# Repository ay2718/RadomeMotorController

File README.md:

# Radome motor controller

## CAN protocol

The Radome CAN protocol is very simple.  Send azimuth commands to address 0x1 and elevation commands to address 0x2.  Azimuth and elevation reply back from addresses 0x101 and 0x102 respectively.  Any packet sent to address 0x0 will trigger both azimuth and elevation to reply back with their current status without initiating a motor movement, sending commands will also trigger a reply back.

Even if you feed the CAN total garbage the dish will not exceed safe positions (for elevation), speeds, or acceleration.

The controllers must be updated at least every 100 ms or faster. Othewise they will safely bring the dish to a halt.

The command structure is as follows:

```
Transmit:
// 2^24 is 360 degrees, position is unsigned
tx byte 0 = position bits 23:16
tx byte 1 = position bits 15:8
tx byte 2 = position bits 7:0

// LSB is 1 arcsecond/s = 1/1200 dps, signed
tx byte 3 = velocity bits 15:8
tx byte 4 = velocity bits 7:0

Receive:
// 2^24 is 360 degrees, position is unsigned
rx byte 0 = position bits 23:16
rx byte 1 = position bits 15:8
rx byte 2 = position bits 7:0

// LSB is 1 arcsecond/s = 1/1200 dps, signed
rx byte 3 = velocity bits 15:8
rx byte 4 = velocity bits 7:0

// LSB is 1 mA, signed
rx byte 5 = current bits 15:8
rx byte 6 = current bits 7:0

// LSB is 0.5V, unsigned
rx byte 7 = bus voltage bits 7:0
```

I recommend casting position as a `uint32_t` such that 2<sup>32</sup> is equivalent to 360 degrees.  This makes position math very nice since overflow lines up with one rotation.

We feed the dish position *and* velocity because the velocity information in order to generate very smooth trajectories.  If you want to command a position and you don't care much about timing, it's fine to send a position command with zero velocity.  If you're tracking a satellite moving a couple degrees per second across the sky on X band, the velocity really helps (empirically we were able to maintain 0.05 degrees of tracking error up to 10 dps or so)

## Firmware overview

If you decide to build the firmware, this is an STM32CubeIDE project.  You may need to enable floating point support for printf.  Define or underine azimuth or elevation in Core/Inc/main.h to set azimuth or elevation.  Encoder offsets are hardcoded in.

## CAN Bootloader usage

`az_bootloader.bin` and `el_bootloader.bin` should already be loaded onto their respective motor drives.  The bootloader takes up 2 flash pages on each drive (4 kB)

`flash_motor.py` is used to upload firmware over CAN bus.  The baud rate is 125000 (same as for operating the drives).

Example usage: `./flash_motor.py` --id 0x01  -f radome_azimuth.bin`.
The `--id` flag selects which drive to write toe (0x01 is azimuth, 0x02 is elevation) and the `-f` or `--filename` flag selects the binfile to upload.

If a motor drive is unresponsive to being flashed, try running `./flash_motor.py ...`, leave it running, and cycle power to the motor drives.  This is useful if there's a problem with the firmware--`flash_motor.py` sends out pings to each motor's address every 100ms and the drives wait for pings in bootloader mode for 500ms before starting up.

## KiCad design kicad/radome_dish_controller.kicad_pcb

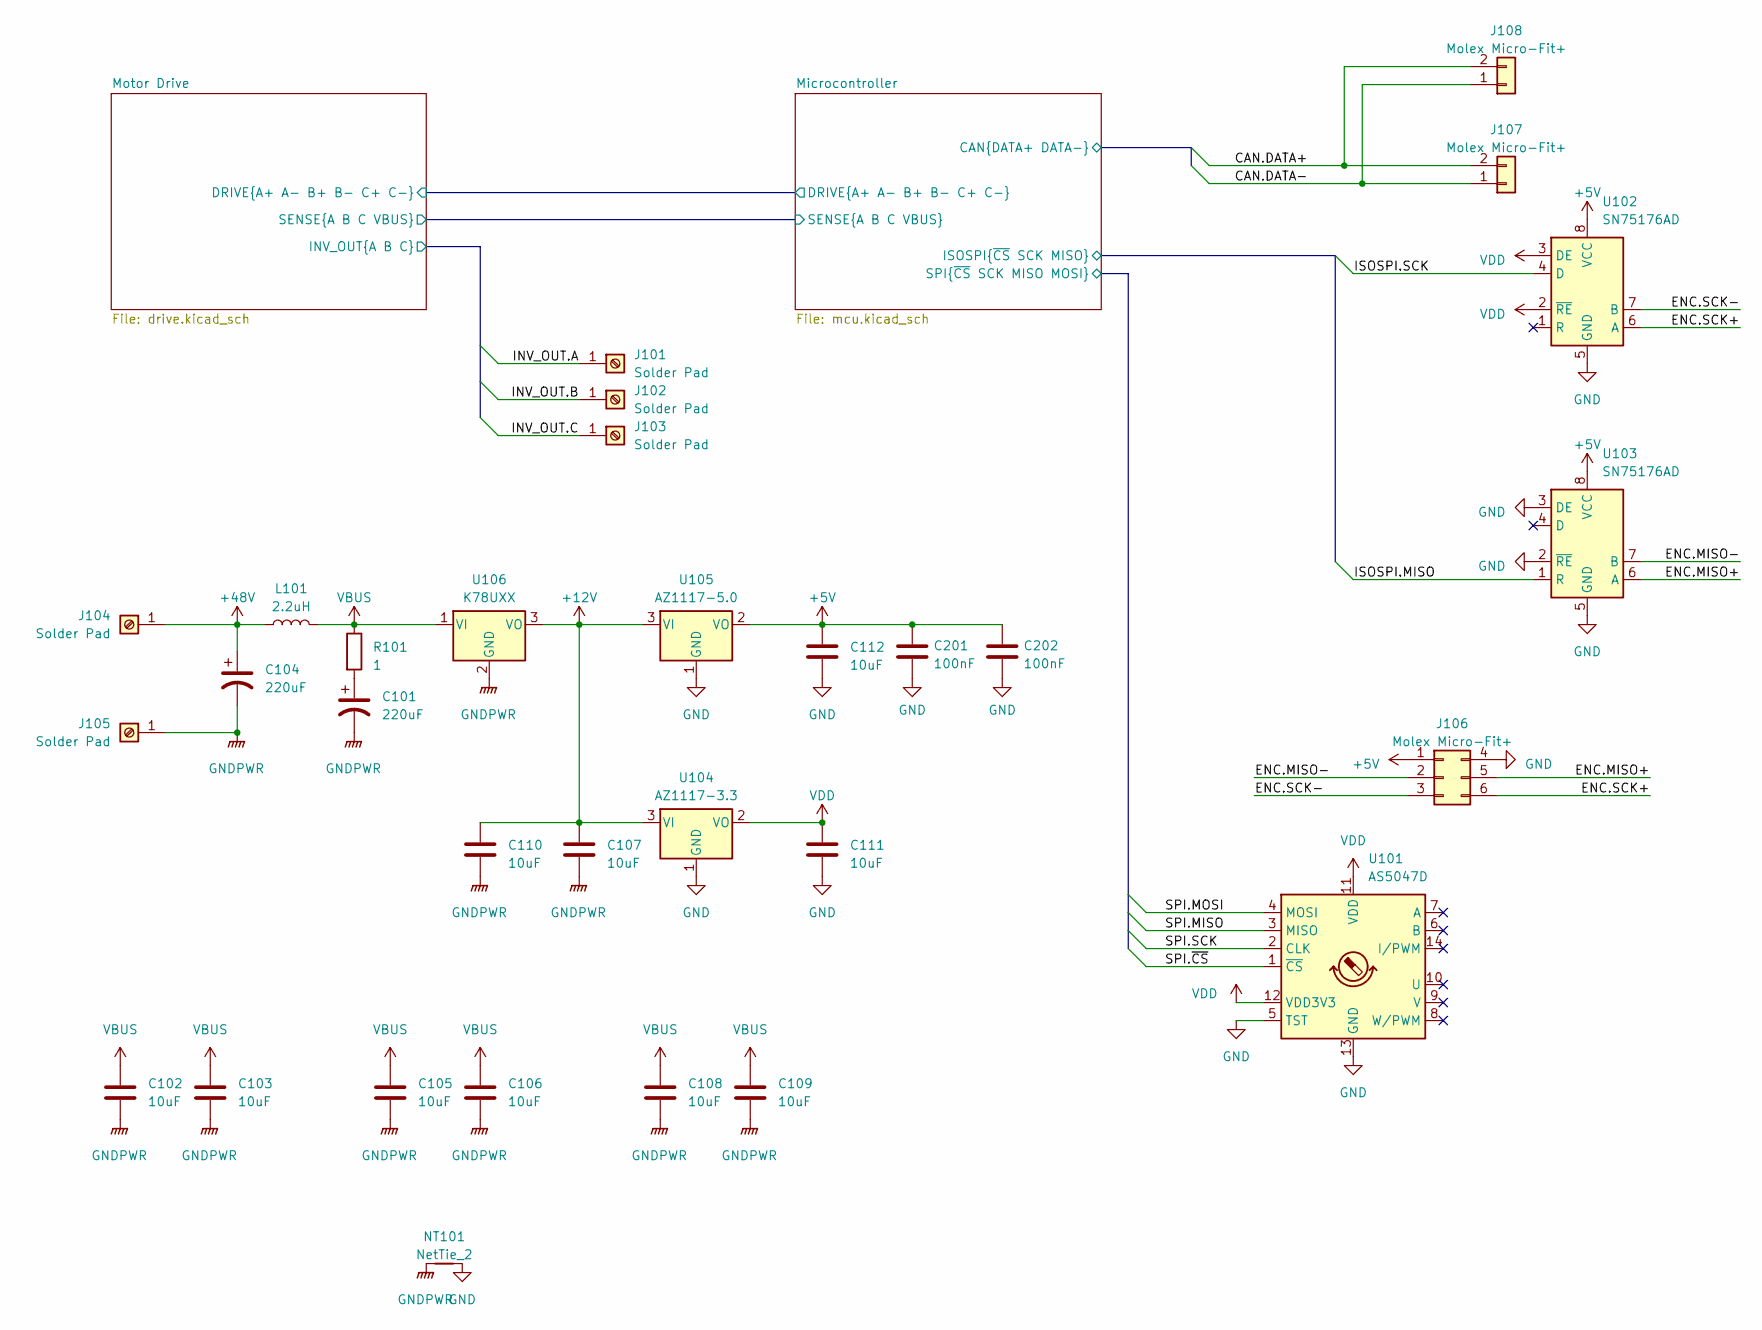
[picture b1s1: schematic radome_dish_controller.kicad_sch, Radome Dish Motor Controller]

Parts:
C101, C104: 220uF; CP_Radial_D12.5mm_P5.00mm
C102, C103, C105, C106, C108, C109: 10uF; C_2220_5650Metric; LCSC C153035
C107, C110, C111, C112: 10uF; C_1206_3216Metric; LCSC C13585
C201, C202: 100nF; C_0603_1608Metric; digikeypn 1276-1935-1-ND
J101, J102, J103, J104, J105: Solder Pad; SolderWirePad_1x01_SMD_5x10mm
J106: Molex Micro-Fit+; MOLEX_2068320602
J107, J108: Molex Micro-Fit+; MOLEX_2165711002
L101: 2.2uH; L_Vishay_IHLP-5050; LCSC C845090
NT101: NetTie_2; NetTie-2_SMD_Pad2.0mm
R101: 1; R_2512_6332Metric; LCSC C11254
U101: AS5047D; TSSOP-14_4.4x5mm_P0.65mm; LCSC C962063
U102, U103: SN75176AD; SOIC-8_3.9x4.9mm_P1.27mm; LCSC C468242
U104: AZ1117-3.3; SOT-223-3_TabPin2; LCSC C435835
U105: AZ1117-5.0; SOT-223-3_TabPin2; LCSC C526405
U106: K78UXX; K78UXX-RightAngle

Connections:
+12V: C107.1, C110.1, U104.3 (VI), U105.3 (VI), U106.3 (VO); also elsewhere on the board
+48V: C104.1, J104.1, L101.1
/ENC.MISO+: J106.5, U103.6 (A)
/ENC.MISO-: J106.2, U103.7 (B)
/ENC.SCK+: J106.6, U102.6 (A)
/ENC.SCK-: J106.3, U102.7 (B)
/Microcontroller/CAN.DATA+: J107.2, J108.2; also elsewhere on the board
/Microcontroller/CAN.DATA-: J107.1, J108.1; also elsewhere on the board
/Microcontroller/ISOSPI.MISO: U103.1 (R); also elsewhere on the board
/Microcontroller/ISOSPI.SCK: U102.4 (D); also elsewhere on the board
/Microcontroller/SPI.MISO: U101.3 (MISO); also elsewhere on the board
/Microcontroller/SPI.MOSI: U101.4 (MOSI); also elsewhere on the board
/Microcontroller/SPI.SCK: U101.2 (CLK); also elsewhere on the board
/Microcontroller/SPI.~CS: U101.1 (~CS); also elsewhere on the board
/Motor Drive/INV_OUT.A: J101.1; also elsewhere on the board
/Motor Drive/INV_OUT.B: J102.1; also elsewhere on the board
/Motor Drive/INV_OUT.C: J103.1; also elsewhere on the board
GND: C111.2, C112.2, C201.2, C202.2, J106.4, NT101.2, U101.5 (TST), U101.13 (GND), U102.5 (GND), U103.2 (~RE), U103.3 (DE), U103.5 (GND), U104.1 (GND), U105.1 (GND); also elsewhere on the board
GNDPWR: C101.2, C102.2, C103.2, C104.2, C105.2, C106.2, C107.2, C108.2, C109.2, C110.2, J105.1, NT101.1, U106.2 (GND); also elsewhere on the board
unnamed: C101.1, R101.2
VBUS: C102.1, C103.1, C105.1, C106.1, C108.1, C109.1, L101.2, R101.1, U106.1 (VI); also elsewhere on the board

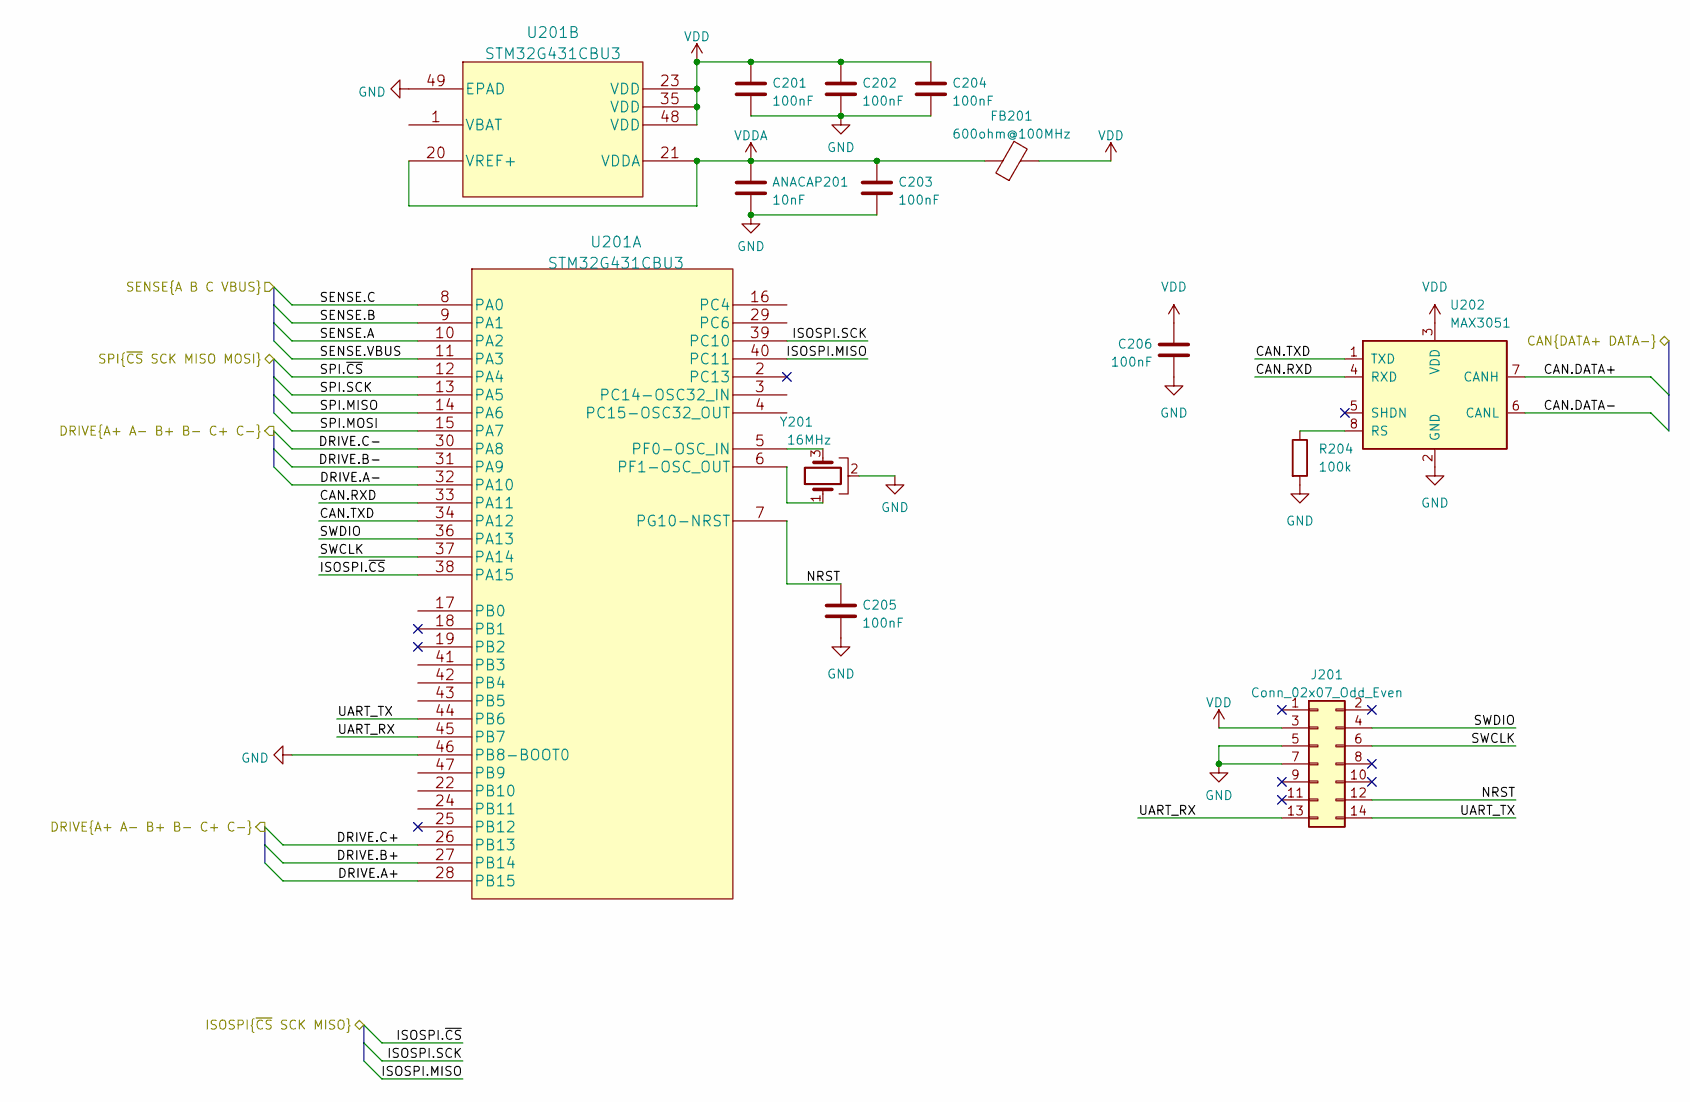
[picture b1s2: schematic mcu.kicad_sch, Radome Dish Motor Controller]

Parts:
ANACAP201: 10nF; C_0603_1608Metric; digikeypn 1276-1009-1-ND
C201, C202, C203, C204, C205, C206: 100nF; C_0603_1608Metric; digikeypn 1276-1935-1-ND
FB201: 600ohm@100MHz; L_0603_1608Metric; digikeypn 732-1593-1-ND
J201: Conn_02x07_Odd_Even; PinHeader_2x07_P1.27mm_Vertical_SMD; digikeypn 1175-1736-ND
R204: 100k; R_0603_1608Metric; LCSC C25803
U201: STM32G431CBU3; QFN-48-1EP_7x7mm_P0.5mm_EP5.3x5.3mm; digikeypn STM32G431CBU3-ND
U202: MAX3051; SO-8_3.9x4.9mm_P1.27mm; LCSC C15648
Y201: 16MHz; Resonator_SMD_Murata_CSTxExxV-3Pin_3.0x1.1mm; digikeypn 490-17948-1-ND

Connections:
/Microcontroller/CAN.DATA+: U202.7 (CANH); also elsewhere on the board
/Microcontroller/CAN.DATA-: U202.6 (CANL); also elsewhere on the board
/Microcontroller/CAN.RXD: U201.33 (PA11), U202.4 (RXD)
/Microcontroller/CAN.TXD: U201.34 (PA12), U202.1 (TXD)
/Microcontroller/DRIVE.A+: U201.28 (PB15); also elsewhere on the board
/Microcontroller/DRIVE.A-: U201.32 (PA10); also elsewhere on the board
/Microcontroller/DRIVE.B+: U201.27 (PB14); also elsewhere on the board
/Microcontroller/DRIVE.B-: U201.31 (PA9); also elsewhere on the board
/Microcontroller/DRIVE.C+: U201.26 (PB13); also elsewhere on the board
/Microcontroller/DRIVE.C-: U201.30 (PA8); also elsewhere on the board
/Microcontroller/ISOSPI.MISO: U201.40 (PC11); also elsewhere on the board
/Microcontroller/ISOSPI.SCK: U201.39 (PC10); also elsewhere on the board
/Microcontroller/ISOSPI.~CS: U201.38 (PA15)
/Microcontroller/NRST: C205.1, J201.12, U201.7 (PG10-NRST)
/Microcontroller/SENSE.A: U201.10 (PA2); also elsewhere on the board
/Microcontroller/SENSE.B: U201.9 (PA1); also elsewhere on the board
/Microcontroller/SENSE.C: U201.8 (PA0); also elsewhere on the board
/Microcontroller/SENSE.VBUS: U201.11 (PA3); also elsewhere on the board
/Microcontroller/SPI.MISO: U201.14 (PA6); also elsewhere on the board
/Microcontroller/SPI.MOSI: U201.15 (PA7); also elsewhere on the board
/Microcontroller/SPI.SCK: U201.13 (PA5); also elsewhere on the board
/Microcontroller/SPI.~CS: U201.12 (PA4); also elsewhere on the board
/Microcontroller/SWCLK: J201.6, U201.37 (PA14)
/Microcontroller/SWDIO: J201.4, U201.36 (PA13)
/Microcontroller/UART_RX: J201.13, U201.45 (PB7)
/Microcontroller/UART_TX: J201.14, U201.44 (PB6)
GND: ANACAP201.2, C201.2, C202.2, C203.2, C204.2, C205.2, C206.2, J201.5, J201.7, R204.2, U201.46 (PB8-BOOT0), U201.49 (EPAD), U202.2 (GND), Y201.2; also elsewhere on the board
unnamed: U201.5 (PF0-OSC_IN), Y201.3
unnamed: U201.6 (PF1-OSC_OUT), Y201.1
unnamed: R204.1, U202.8 (RS)
VDDA: ANACAP201.1, C203.1, FB201.1, U201.20 (VREF+), U201.21 (VDDA)

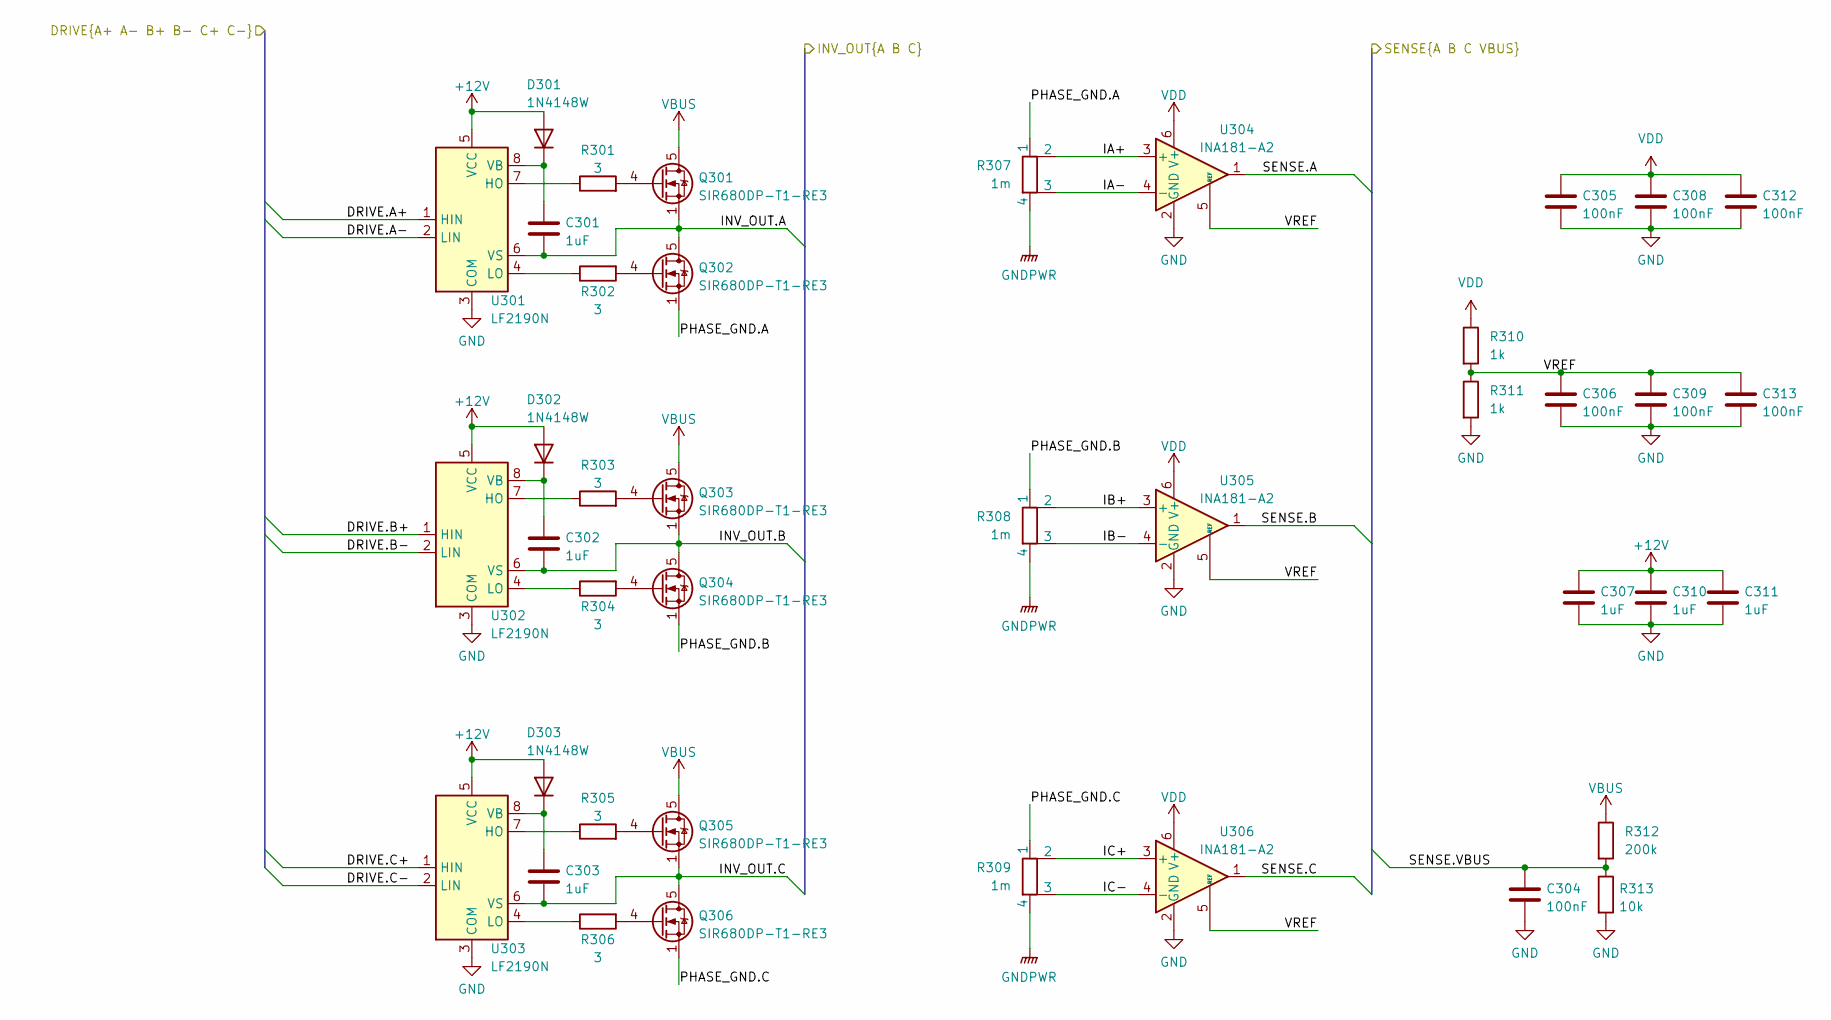
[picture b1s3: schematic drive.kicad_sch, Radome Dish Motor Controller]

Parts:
C301, C302, C303, C307, C310, C311: 1uF; C_0603_1608Metric; digikeypn 1276-1860-1-ND
C304, C305, C306, C308, C309, C312, C313: 100nF; C_0603_1608Metric; digikeypn 1276-1935-1-ND
D301, D302, D303: 1N4148W; D_SOD-123; digikeypn 1N4148W-13FDICT-ND
Q301, Q302, Q303, Q304, Q305, Q306: SIR680DP-T1-RE3; PowerPAK_SO-8_Single; digikeypn SIR426DP-T1-GE3CT-ND
R301, R302, R303, R304, R305, R306: 3; R_0603_1608Metric; digikeypn RMCF0603FT3R00CT-ND
R307, R308, R309: 1m; R_Shunt_Vishay_WSK2512_6332Metric_T2.21mm; LCSC C459678
R310, R311: 1k; R_0603_1608Metric; digikeypn RMCF0603FT10K0CT-ND
R312: 200k; R_0603_1608Metric; digikeypn CR0603-FX-5102ELFCT-ND
R313: 10k; R_0603_1608Metric; digikeypn RMCF0603FT10K0CT-ND
U301, U302, U303: LF2190N; SOIC-8_3.9x4.9mm_P1.27mm; digikeypn 212-LF2190NTRCT-ND
U304, U305, U306: INA181-A2; SOT-23-6; digikeypn 296-47657-1-ND

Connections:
+12V: C307.1, C310.1, C311.1, D301.2 (A), D302.2 (A), D303.2 (A), U301.5 (VCC), U302.5 (VCC), U303.5 (VCC); also elsewhere on the board
/Microcontroller/DRIVE.A+: U301.1 (HIN); also elsewhere on the board
/Microcontroller/DRIVE.A-: U301.2 (LIN); also elsewhere on the board
/Microcontroller/DRIVE.B+: U302.1 (HIN); also elsewhere on the board
/Microcontroller/DRIVE.B-: U302.2 (LIN); also elsewhere on the board
/Microcontroller/DRIVE.C+: U303.1 (HIN); also elsewhere on the board
/Microcontroller/DRIVE.C-: U303.2 (LIN); also elsewhere on the board
/Microcontroller/SENSE.A: U304.1; also elsewhere on the board
/Microcontroller/SENSE.B: U305.1; also elsewhere on the board
/Microcontroller/SENSE.C: U306.1; also elsewhere on the board
/Microcontroller/SENSE.VBUS: C304.1, R312.2, R313.1; also elsewhere on the board
/Motor Drive/IA+: R307.2, U304.3 (+)
/Motor Drive/IA-: R307.3, U304.4 (-)
/Motor Drive/IB+: R308.2, U305.3 (+)
/Motor Drive/IB-: R308.3, U305.4 (-)
/Motor Drive/IC+: R309.2, U306.3 (+)
/Motor Drive/IC-: R309.3, U306.4 (-)
/Motor Drive/INV_OUT.A: C301.2, Q301.1 (S), Q301.2 (S), Q301.3 (S), Q302.5 (D), U301.6 (VS); also elsewhere on the board
/Motor Drive/INV_OUT.B: C302.2, Q303.1 (S), Q303.2 (S), Q303.3 (S), Q304.5 (D), U302.6 (VS); also elsewhere on the board
/Motor Drive/INV_OUT.C: C303.2, Q305.1 (S), Q305.2 (S), Q305.3 (S), Q306.5 (D), U303.6 (VS); also elsewhere on the board
/Motor Drive/PHASE_GND.A: Q302.1 (S), Q302.2 (S), Q302.3 (S), R307.1
/Motor Drive/PHASE_GND.B: Q304.1 (S), Q304.2 (S), Q304.3 (S), R308.1
/Motor Drive/PHASE_GND.C: Q306.1 (S), Q306.2 (S), Q306.3 (S), R309.1
/Motor Drive/VREF: C306.1, C309.1, C313.1, R310.2, R311.1, U304.5 (REF), U305.5 (REF), U306.5 (REF)
GND: C304.2, C305.2, C306.2, C307.2, C308.2, C309.2, C310.2, C311.2, C312.2, C313.2, R311.2, R313.2, U301.3 (COM), U302.3 (COM), U303.3 (COM), U304.2 (GND), U305.2 (GND), U306.2 (GND); also elsewhere on the board
GNDPWR: R307.4, R308.4, R309.4; also elsewhere on the board
unnamed: C301.1, D301.1 (K), U301.8 (VB)
unnamed: C302.1, D302.1 (K), U302.8 (VB)
unnamed: C303.1, D303.1 (K), U303.8 (VB)
unnamed: Q301.4 (G), R301.2
unnamed: Q302.4 (G), R302.2
unnamed: Q303.4 (G), R303.2
unnamed: Q304.4 (G), R304.2
unnamed: Q305.4 (G), R305.2
unnamed: Q306.4 (G), R306.2
unnamed: R301.1, U301.7 (HO)
unnamed: R302.1, U301.4 (LO)
unnamed: R303.1, U302.7 (HO)
unnamed: R304.1, U302.4 (LO)
unnamed: R305.1, U303.7 (HO)
unnamed: R306.1, U303.4 (LO)
VBUS: Q301.5 (D), Q303.5 (D), Q305.5 (D), R312.1; also elsewhere on the board

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
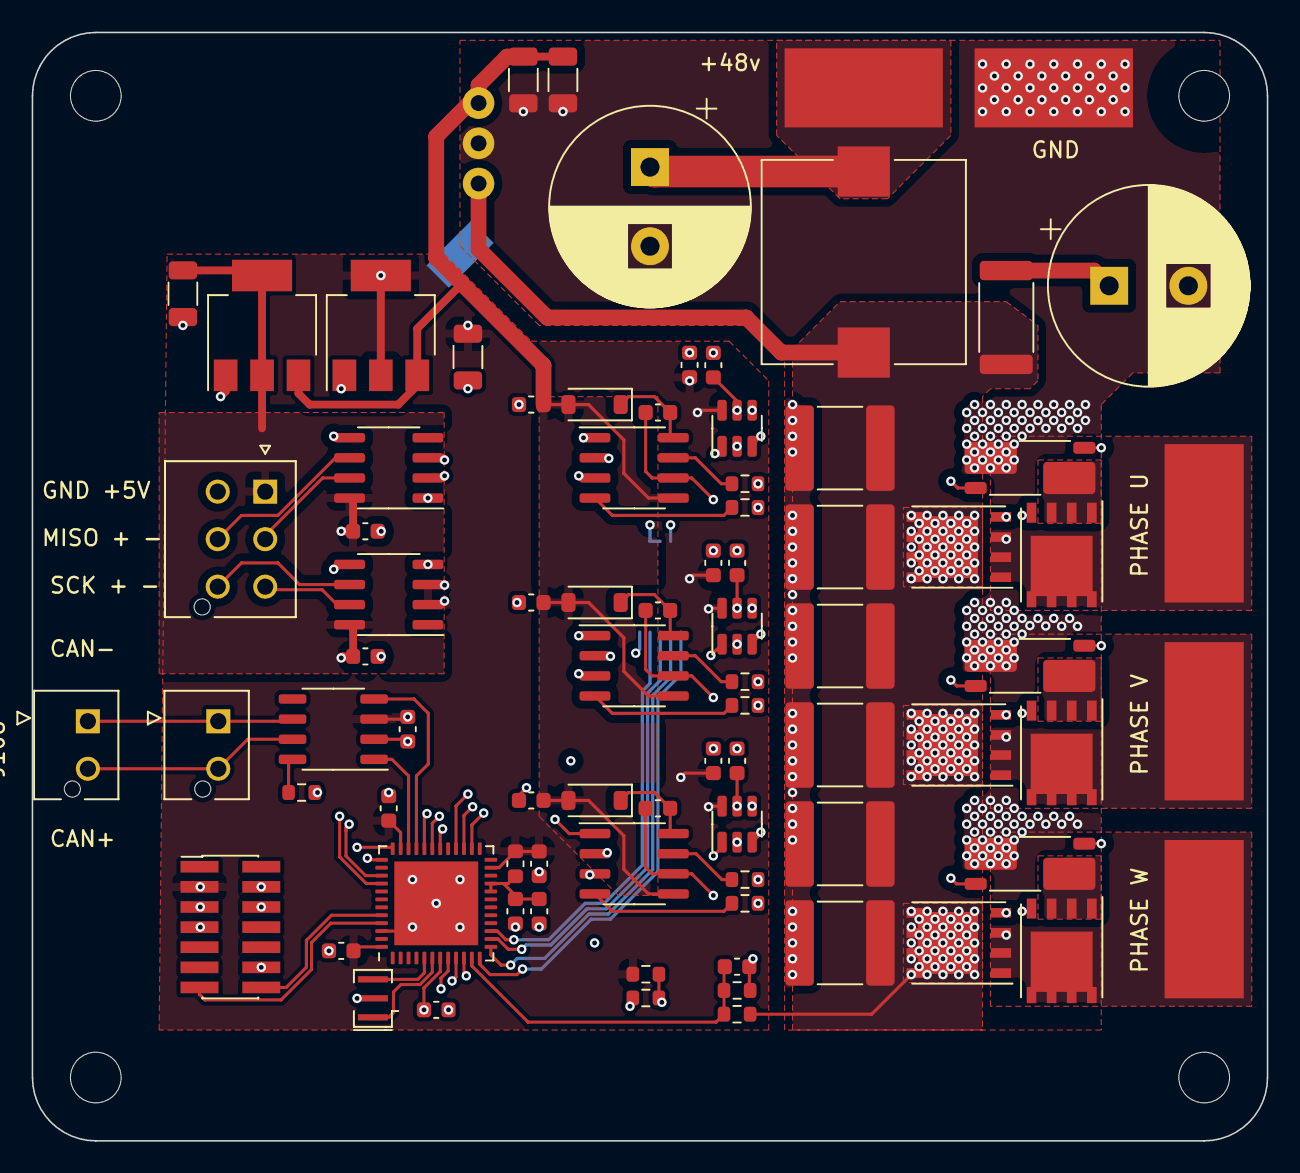
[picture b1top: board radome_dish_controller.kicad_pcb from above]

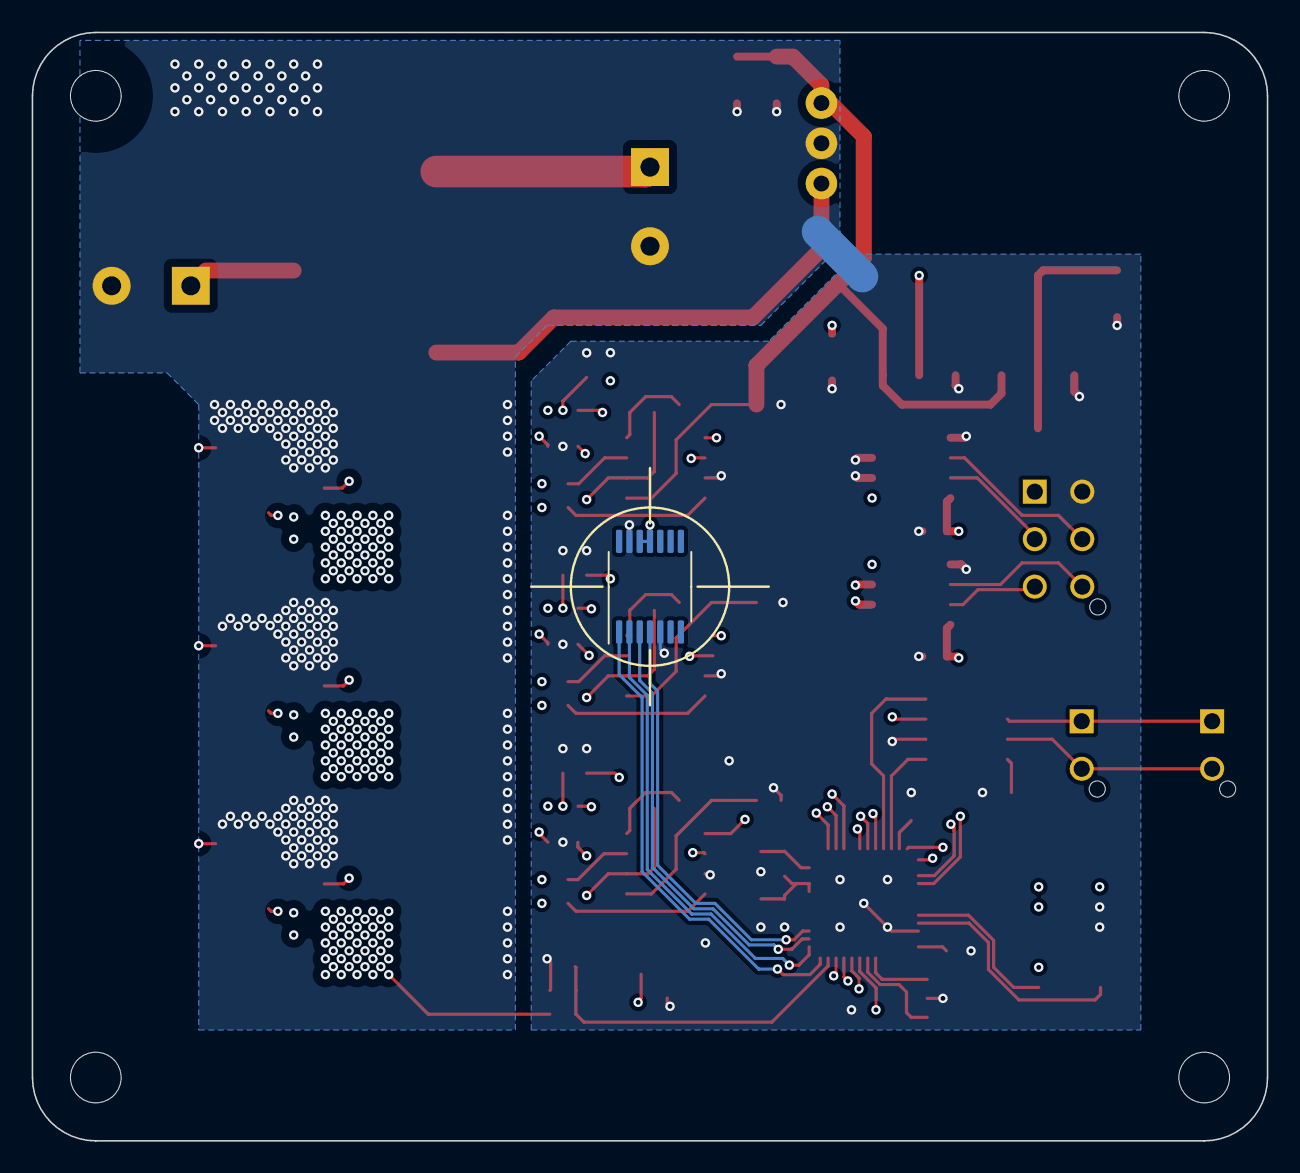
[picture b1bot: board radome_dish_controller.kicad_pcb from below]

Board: 4 copper layers, 78.0 x 70.0 mm, 85 parts (2 on the bottom side), 69 nets.

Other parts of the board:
C113, C114: 100nF; C_0603_1608Metric

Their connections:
GND: C113.2, C114.2; also elsewhere on the board

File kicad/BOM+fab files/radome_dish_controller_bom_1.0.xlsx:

Component | Description | Part | References | Value | Footprint | Quantity Per PCB | Datasheet | LCSC | digikeypn | P/N
1 | Unpolarized capacitor | C | ANACAP201 | 10nF | C_0603_1608Metric | 1 | ~ | C1589 | 1276-1009-1-ND
2 | Unpolarized capacitor | C | C113 C114 C201 C202 C203 C204 C205 C206 C304 C305 C306 C308 C309 C312 C313 | 100nF | C_0603_1608Metric | 15 | ~ | C1591 | 1276-1935-1-ND
3 | Unpolarized capacitor | C | C102 C103 C105 C106 C108 C109 | 10uF | C_2220_5650Metric | 6 | ~ | C153035
4 | Unpolarized capacitor | C | C107 C110 C111 C112 | 10uF | C_1206_3216Metric | 4 | ~ | C13585
5 | Unpolarized capacitor | C | C301 C302 C303 C307 C310 C311 | 1uF | C_0603_1608Metric | 6 | ~ | C15849 | 1276-1860-1-ND
6 | Polarized capacitor, US symbol | C_Polarized_US | C101 C104 | 220uF | CP_Radial_D12.5mm_P5.00mm | 2 | ~
7 | 75V 0.15A Fast Switching Diode, SOD-123 | 1N4148W | D301 D302 D303 | 1N4148W | D_SOD-123 | 3 | https://www.vishay.com/docs/85748/1n4148w.pdf | C112342 | 1N4148W-13FDICT-ND
8 | Ferrite bead | FerriteBead | FB201 | 600ohm@100MHz | L_0603_1608Metric | 1 | ~ | C20345 | 732-1593-1-ND
9 | Generic connector, double row, 02x07, odd/even pin numbering scheme (row 1 odd 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 | Conn_02x07_Odd_Even | J201 | Conn_02x07_Odd_Even | PinHeader_2x07_P1.27mm_Vertical_SMD | 1 | ~ | C5445007 | 1175-1736-ND
10 | Generic connector, double row, 02x03, top/bottom pin numbering scheme (row 1: 1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 | Conn_02x03_Top_Bottom | J106 | Molex Micro-Fit+ | MOLEX_2068320602 | 1 | ~
11 | Generic connector, single row, 01x02, script generated (kicad-library-utils/sch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 | Conn_01x02 | J107 J108 | Molex Micro-Fit+ | MOLEX_2165711002 | 2 | ~
12 | Generic screw terminal, single row, 01x01, script generated (kicad-library-util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 | Screw_Terminal_01x01 | J101 J102 J103 J104 J105 | Solder Pad | SolderWirePad_1x01_SMD_5x10mm | 5 | ~
13 | Inductor | L | L101 | 2.2uH | L_Vishay_IHLP-5050 | 1 | https://www.vishay.com/docs/34337/ihlp5050fd5a.pdf | C845090 |  | IHLP5050FDER2R2M5A
14 | 30A Id, 30V Vds, 2.4mOhm Ron, PowerPAK-8 | Si7336ADP | Q301 Q302 Q303 Q304 Q305 Q306 | SIR680DP-T1-RE3 | PowerPAK_SO-8_Single | 6 | https://www.vishay.com/docs/65162/sir426dp.pdf |  | SIR426DP-T1-GE3CT-ND
15 | Resistor | R | R101 | 1 | R_2512_6332Metric | 1 | ~ | C11254
16 | Resistor | R | R204 | 100k | R_0603_1608Metric | 1 | ~ | C25803
17 | Resistor | R | R313 | 10k | R_0603_1608Metric | 1 | ~ | C859110 | RMCF0603FT10K0CT-ND
18 | Resistor | R | R310 R311 | 1k | R_0603_1608Metric | 2 | ~ | C2924142 | RMCF0603FT10K0CT-ND
19 | Shunt resistor | R_Shunt | R307 R308 R309 | 1m | R_Shunt_Vishay_WSK2512_6332Metric_T2.21mm | 3 | ~ | C459678
20 | Resistor | R | R312 | 200k | R_0603_1608Metric | 1 | ~ | C25811 | CR0603-FX-5102ELFCT-ND
21 | Resistor | R | R301 R302 R303 R304 R305 R306 | 3 | R_0603_1608Metric | 6 | ~ | C137724 | RMCF0603FT3R00CT-ND
22 | On-Axis Magnetic Position Sensor, 14-bit, PWM Output, ABI Output, UVW Output, S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 | AS5047D | U101 | AS5047D | TSSOP-14_4.4x5mm_P0.65mm | 1 | https://ams.com/documents/20143/36005/AS5047D_DS000394_2-00.pdf | C962063
23 | 1A 20V Fixed LDO Linear Regulator, 3.3V, SOT-89/SOT-223/TO-220/TO-252/TO-263 | AZ1117-3.3 | U104 | AZ1117-3.3 | SOT-223-3_TabPin2 | 1 | https://www.diodes.com/assets/Datasheets/AZ1117.pdf | C435835
24 | 1A 20V Fixed LDO Linear Regulator, 5.0V, SOT-89/SOT-223/TO-220/TO-252/TO-263 | AZ1117-5.0 | U105 | AZ1117-5.0 | SOT-223-3_TabPin2 | 1 | https://www.diodes.com/assets/Datasheets/AZ1117.pdf | C526405
25 | Bidirectional, Low- and High-Side Voltage Output, Current-Sense Amplifier, SOT-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 | INA181 | U304 U305 U306 | INA181-A2 | SOT-23-6 | 3 | http://www.ti.com/lit/ds/symlink/ina181.pdf | C116200 | 296-47657-1-ND
26 | DC/DC buck converter | K78UXX | U106 | K78UXX | K78UXX-RightAngle | 1 | https://www.mornsun-power.com/html/pdf/K78U12-500R3L.html
27 | High and Low Side Driver, 600V, 1.4/1.8A, PDIP-8/SOIC-8 | IRS2181 | U301 U302 U303 | LF2190N | SOIC-8_3.9x4.9mm_P1.27mm | 3 | https://www.littelfuse.com/~/media/electronics/datasheets/po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 | C3655431 | 212-LF2190NTRCT-ND
28 | High-Speed CAN Transceiver, 1Mbps, 3.3V supply | MAX3051 | U202 | MAX3051 | SO-8_3.9x4.9mm_P1.27mm | 1 | http://datasheets.maximintegrated.com/en/ds/MAX3051.pdf | C15648
29 | Differential RS-422/RS-485 bus transceiver, SOIC-8 | SN75176AD | U102 U103 | SN75176AD | SOIC-8_3.9x4.9mm_P1.27mm | 2 | http://www.ti.com/lit/ds/symlink/sn75176a.pdf | C468242
30 |  | STM32G431CBU3_1 | U201 | STM32G431CBU3 | QFN-48-1EP_7x7mm_P0.5mm_EP5.3x5.3mm | 1 |  | C529356 | STM32G431CBU3-ND
31 | Three pin crystal, GND on pin 2 | Crystal_GND2 | Y201 | 16MHz | Resonator_SMD_Murata_CSTxExxV-3Pin_3.0x1.1mm | 1 | ~ | C341521 | 490-17948-1-ND
Component Groups: | 31
Component Count: | 84
Fitted Components: | 84
Number of PCBs: | 1
Total components: | 84
Schematic Version: | 1.0
Schematic Date: | 2023-03-29
BoM Date: | Sat 01 Jul 2023 03:16:00 PM EDT
Schematic Source: | radome_dish_controller.kicad_sch
KiCad Version: | Eeschema 7.0.5-1.fc38

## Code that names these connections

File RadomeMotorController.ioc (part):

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Mcu.Name=STM32G431C(6-8-B)Ux
Mcu.Package=UFQFPN48
Mcu.UserName=STM32G431CBUx
PA0.GPIOParameters=GPIO_Label
PA0.GPIO_Label=SOC
PA0.Mode=IN1-Single-Ended
PA0.Signal=ADC2_IN1
PA1.GPIOParameters=GPIO_Label
PA1.GPIO_Label=SOB
PA1.Mode=IN2-Single-Ended
PA1.Signal=ADC2_IN2
PA10.Signal=S_TIM1_CH3
PA11.Mode=FDCAN_Activate
PA11.Signal=FDCAN1_RX
PA12.Mode=FDCAN_Activate
PA12.Signal=FDCAN1_TX
PA13.Mode=Serial_Wire
PA13.Signal=SYS_JTMS-SWDIO
PA14.Mode=Serial_Wire
PA14.Signal=SYS_JTCK-SWCLK
PA15.Signal=GPIO_Output
PA2.GPIOParameters=GPIO_Label
PA2.GPIO_Label=SOA
PA2.Mode=IN3-Single-Ended
PA2.Signal=ADC1_IN3
PA3.GPIOParameters=GPIO_Label
PA3.GPIO_Label=VBUS_SENSE
PA3.Mode=IN4-Single-Ended
PA3.Signal=ADC1_IN4
PA4.GPIOParameters=GPIO_Label
PA4.GPIO_Label=SPI1_CS
PA4.Signal=GPIO_Output
PA5.Mode=Full_Duplex_Master
PA5.Signal=SPI1_SCK
PA6.Mode=Full_Duplex_Master
PA6.Signal=SPI1_MISO
PA7.Mode=Full_Duplex_Master
PA7.Signal=SPI1_MOSI
PA8.Signal=S_TIM1_CH1
PA9.Signal=S_TIM1_CH2
PB13.Mode=PWM Generation1 CH1 CH1N
PB13.Signal=TIM1_CH1N
PB14.Mode=PWM Generation2 CH2 CH2N
PB14.Signal=TIM1_CH2N
PB15.Mode=PWM Generation3 CH3 CH3N
PB15.Signal=TIM1_CH3N
PB6.Mode=Asynchronous
PB6.Signal=USART1_TX
PB7.Mode=Asynchronous
PB7.Signal=USART1_RX
PC10.Mode=RX_Only_Simplex_Unidirect_Master
PC10.Signal=SPI3_SCK
PC11.Mode=RX_Only_Simplex_Unidirect_Master
PC11.Signal=SPI3_MISO
PF0-OSC_IN.Mode=HSE-External-Oscillator
PF0-OSC_IN.Signal=RCC_OSC_IN
PF1-OSC_OUT.Mode=HSE-External-Oscillator
PF1-OSC_OUT.Signal=RCC_OSC_OUT
RCC.HSE_VALUE=16000000
RCC.SYSCLKFreq_VALUE=170000000
RCC.SYSCLKSource=RCC_SYSCLKSOURCE_PLLCLK
board=custom

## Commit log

2024-11-25 add CAN bootloader, change elevation limit to 87 degrees
2025-09-02 Added kicad files for radome controller
2025-09-02 add schematic pdf
